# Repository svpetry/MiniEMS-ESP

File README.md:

# MiniEMS-ESP

Small EMS-ESP board that is powered by the EMS bus.

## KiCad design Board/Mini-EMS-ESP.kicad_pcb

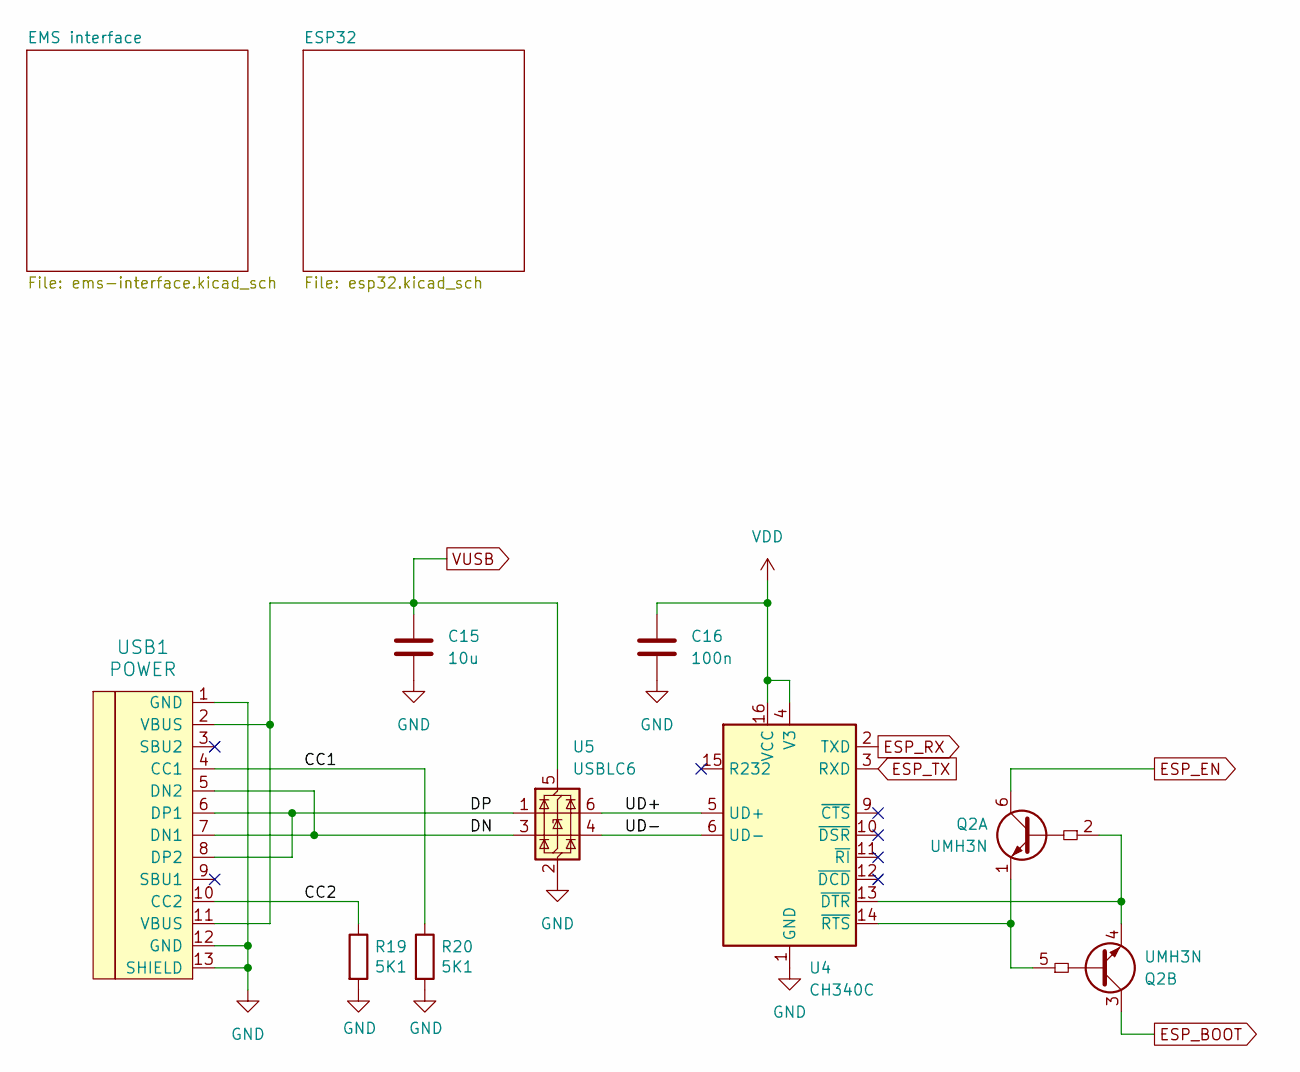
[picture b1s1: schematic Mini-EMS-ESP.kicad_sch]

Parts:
C15: 10u; C_1206_3216Metric
C16: 100n; C_0805_2012Metric
Q2: UMH3N; SOT-363_SC-70-6
R19, R20: 5K1; R_0805_2012Metric
U4: CH340C; SOIC-16_3.9x9.9mm_P1.27mm
U5: USBLC6; SOT-23-6
USB1: POWER; HRO-TYPE-C-31-M-12

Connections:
/CC1: R20.1, USB1.4 (CC1)
/CC2: R19.1, USB1.10 (CC2)
/DN: U5.3 (I/O2), USB1.5 (DN2), USB1.7 (DN1)
/DP: U5.1 (I/O1), USB1.6 (DP1), USB1.8 (DP2)
/UD+: U4.5 (UD+), U5.6 (I/O1)
/UD-: U4.6 (UD-), U5.4 (I/O2)
ESP_BOOT: Q2.3 (C2); also elsewhere on the board
ESP_EN: Q2.6 (C1); also elsewhere on the board
ESP_RX: U4.2 (TXD); also elsewhere on the board
ESP_TX: U4.3 (RXD); also elsewhere on the board
GND: C15.2, C16.2, R19.2, R20.2, U4.1 (GND), U5.2 (GND), USB1.1 (GND), USB1.12 (GND), USB1.13 (SHIELD); also elsewhere on the board
unnamed: Q2.2 (B1), Q2.4 (E2), U4.13 (~DTR)
unnamed: Q2.1 (E1), Q2.5 (B2), U4.14 (~RTS)
VDD: C16.1, U4.4 (V3), U4.16 (VCC); also elsewhere on the board
VUSB: C15.1, U5.5 (VBUS), USB1.2 (VBUS), USB1.11 (VBUS); also elsewhere on the board

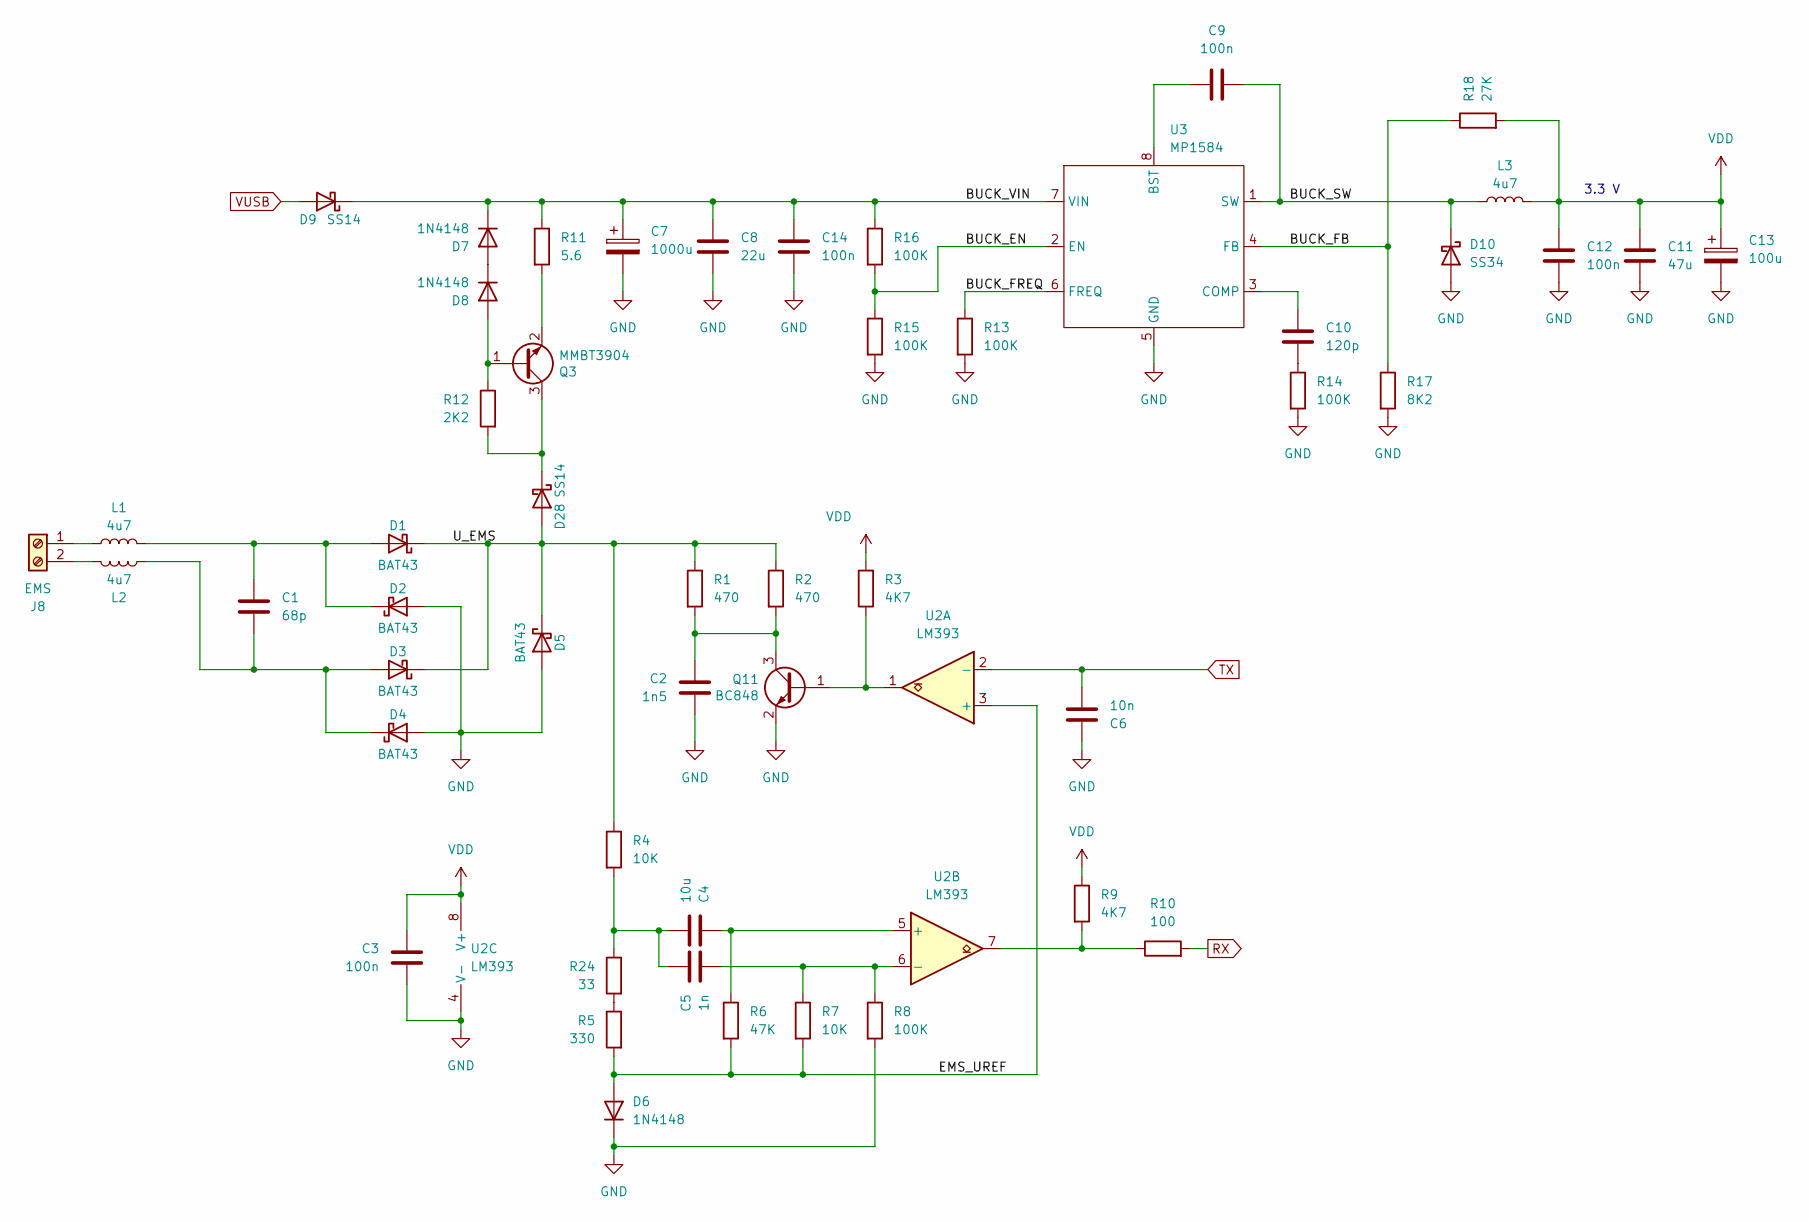
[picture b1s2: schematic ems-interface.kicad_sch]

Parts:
C1: 68p; C_0805_2012Metric
C2: 1n5; C_0805_2012Metric
C3, C9, C12, C14: 100n; C_0805_2012Metric
C4: 10u; C_1206_3216Metric
C5: 1n; C_0805_2012Metric
C6: 10n; C_0805_2012Metric
C7: 1000u; CP_Elec_10x10.5
C8: 22u; C_1206_3216Metric
C10: 120p; C_0805_2012Metric
C11: 47u; C_1206_3216Metric
C13: 100u; CP_Elec_5x5.4
D1, D2, D3, D4, D5: BAT43; D_SOD-123
D6, D7, D8: 1N4148; D_SOD-123
D9, D28: SS14; D_SMA
D10: SS34; D_SMA
J8: EMS; Altech_AK100_1x02_P5.00mm
L1, L2: 4u7; L_1206_3216Metric
L3: 4u7; L_APV_APH0650
Q3: MMBT3904; SOT-23
Q11: BC848; SOT-23
R1, R2: 470; R_1206_3216Metric
R3, R9: 4K7; R_0805_2012Metric
R4, R7: 10K; R_0805_2012Metric
R5: 330; R_0805_2012Metric
R6: 47K; R_0805_2012Metric
R8, R13, R14, R15, R16: 100K; R_0805_2012Metric
R10: 100; R_0805_2012Metric
R11: 5.6; R_0805_2012Metric
R12: 2K2; R_0805_2012Metric
R17: 8K2; R_0805_2012Metric
R18: 27K; R_0805_2012Metric
R24: 33; R_0805_2012Metric
U2: LM393; SOIC-8_3.9x4.9mm_P1.27mm
U3: MP1584; SOIC-8_3.9x4.9mm_P1.27mm

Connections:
/EMS interface/BUCK_EN: R15.1, R16.2, U3.2 (EN)
/EMS interface/BUCK_FB: R17.1, R18.1, U3.4 (FB)
/EMS interface/BUCK_FREQ: R13.1, U3.6 (FREQ)
/EMS interface/BUCK_SW: C9.2, D10.1 (K), L3.1, U3.1 (SW)
/EMS interface/BUCK_VIN: C7.1, C8.1, C14.1, D7.1 (K), D9.1 (K), R11.1, R16.1, U3.7 (VIN)
/EMS interface/EMS_UREF: D6.2 (A), R5.2, R6.2, R7.2, U2.3 (+)
/EMS interface/U_EMS: D1.1 (K), D3.1 (K), D5.1 (K), D28.2 (A), R1.1, R2.1, R4.1
GND: C2.2, C3.2, C6.1, C7.2, C8.2, C11.2, C12.2, C13.2, C14.2, D2.2 (A), D4.2 (A), D5.2 (A), D6.1 (K), D10.2 (A), Q11.2 (E), R8.2, R13.2, R14.2, R15.2, R17.2, U2.4 (V-), U3.5 (GND); also elsewhere on the board
unnamed: C4.2, C5.1, R4.2, R24.1
unnamed: C10.1, R14.1
unnamed: C1.1, D1.2 (A), D2.1 (K), L1.2
unnamed: C1.2, D3.2 (A), D4.1 (K), L2.2
unnamed: D7.2 (A), D8.1 (K)
unnamed: D8.2 (A), Q3.1 (B), R12.1
unnamed: D28.1 (K), Q3.3 (C), R12.2
unnamed: J8.1, L1.1
unnamed: J8.2, L2.1
unnamed: Q3.2 (E), R11.2
unnamed: Q11.1 (B), R3.1, U2.1
unnamed: C2.1, Q11.3 (C), R1.2, R2.2
unnamed: R9.2, R10.1, U2.7
unnamed: R5.1, R24.2
unnamed: C4.1, R6.1, U2.5 (+)
unnamed: C5.2, R7.1, R8.1, U2.6 (-)
unnamed: C9.1, U3.8 (BST)
unnamed: C10.2, U3.3 (COMP)
RX: R10.2; also elsewhere on the board
TX: C6.2, U2.2 (-); also elsewhere on the board
VDD: C3.1, C11.1, C12.1, C13.1, L3.2, R3.2, R9.1, R18.2, U2.8 (V+); also elsewhere on the board
VUSB: D9.2 (A); also elsewhere on the board

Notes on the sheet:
3.3 V

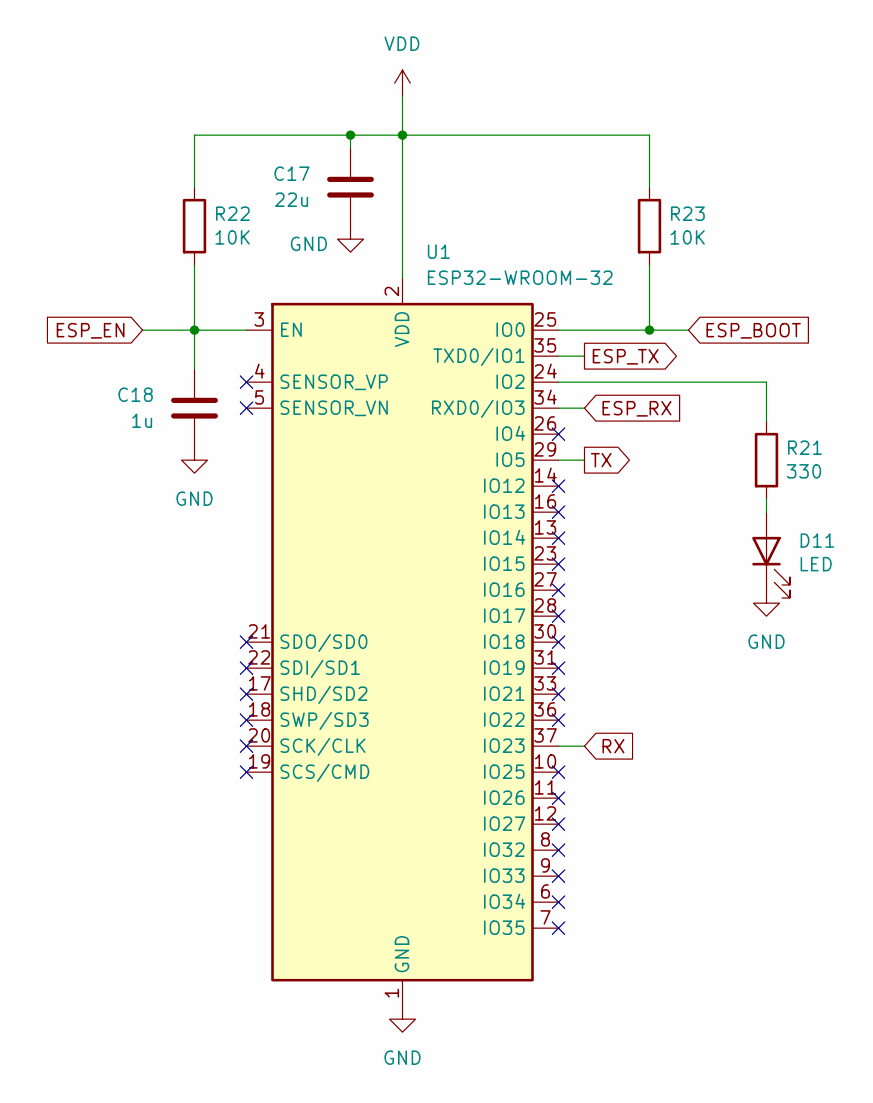
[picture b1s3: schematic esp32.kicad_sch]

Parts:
C17: 22u; C_1206_3216Metric
C18: 1u; C_0805_2012Metric
D11: LED; LED_0805_2012Metric
R21: 330; R_0805_2012Metric
R22, R23: 10K; R_0805_2012Metric
U1: ESP32-WROOM-32

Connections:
ESP_BOOT: R23.2, U1.25 (IO0); also elsewhere on the board
ESP_EN: C18.1, R22.2, U1.3 (EN); also elsewhere on the board
ESP_RX: U1.34 (RXD0/IO3); also elsewhere on the board
ESP_TX: U1.35 (TXD0/IO1); also elsewhere on the board
GND: C17.1, C18.2, D11.1 (K), U1.1 (GND), U1.15 (GND), U1.38 (GND), U1.39 (GND); also elsewhere on the board
unnamed: D11.2 (A), R21.2
unnamed: R21.1, U1.24 (IO2)
RX: U1.37 (IO23); also elsewhere on the board
TX: U1.29 (IO5); also elsewhere on the board
VDD: C17.2, R22.1, R23.1, U1.2 (VDD); also elsewhere on the board

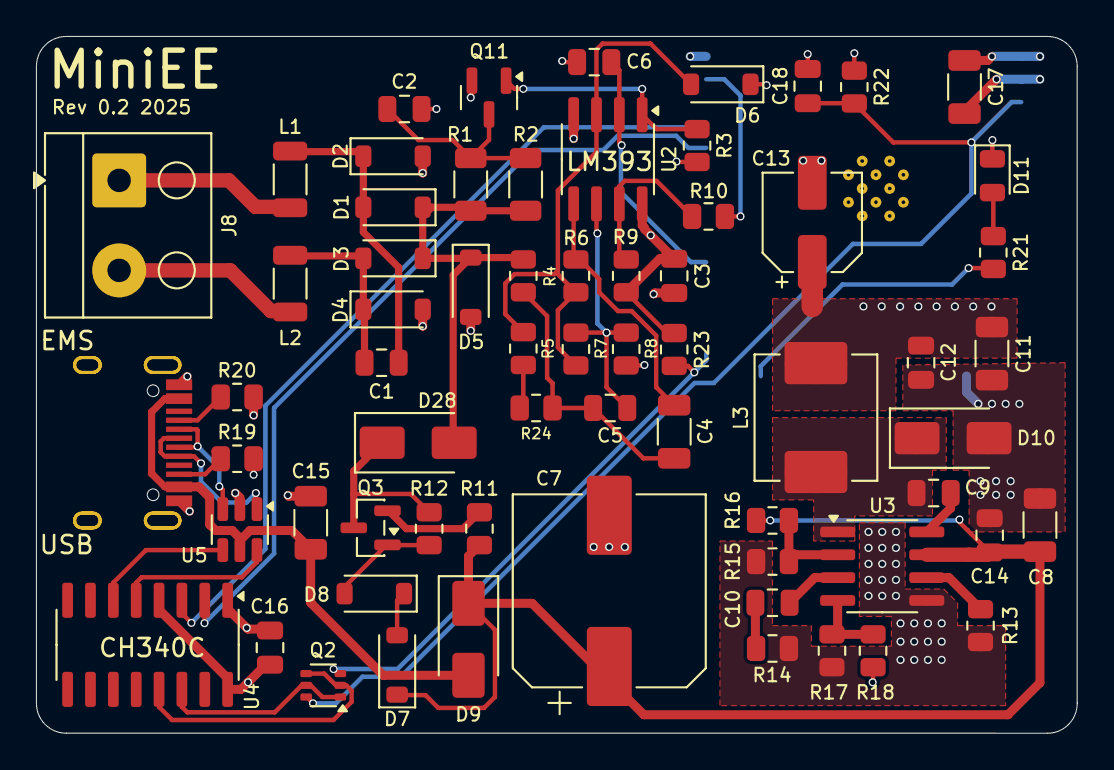
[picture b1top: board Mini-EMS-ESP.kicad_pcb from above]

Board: 4 copper layers, 57.8 x 38.7 mm, 67 parts (1 on the bottom side), 44 nets.

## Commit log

2025-10-09 Adds board and doc
2025-10-09 Rev 0.1
2025-10-14 Minor fixes
2025-10-19 Fixes values
2025-10-22 Minor fixes and improvements. Changes board shape.
2025-10-24 Fixes constant current circuit.
2025-10-24 Replaces Q3 with higher current type
2025-10-25 Rev 0.2
2025-10-25 gitignore update
